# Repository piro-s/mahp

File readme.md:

# Music mini-amplifier with indicator:  
A simple two-channel amplifier on a chip TDA2822 with indicator.  

### Schemes:  
###### Amplifier_v0.1:  
[pdf](amplifier/docs/mahp_v0.1.pdf)  
###### Indicator_v0.1:  
[pdf](indicator/docs/indicator_v0.1.pdf)  

### Images:  
###### Amplifier_v0.1:  
top:  
  
bottom:  

###### Indicator_v0.1:  
top:  
  
bottom:  

###### gerber:  
Archive for production:  
[Amplifier_v0.1](https://github.com/piro-s/mahp/raw/master/amplifier/gerber/mahp_v0.1.zip)  
[Indicator_v0.1](https://github.com/piro-s/mahp/raw/master/indicator/gerber/indicator_v0.1.zip)

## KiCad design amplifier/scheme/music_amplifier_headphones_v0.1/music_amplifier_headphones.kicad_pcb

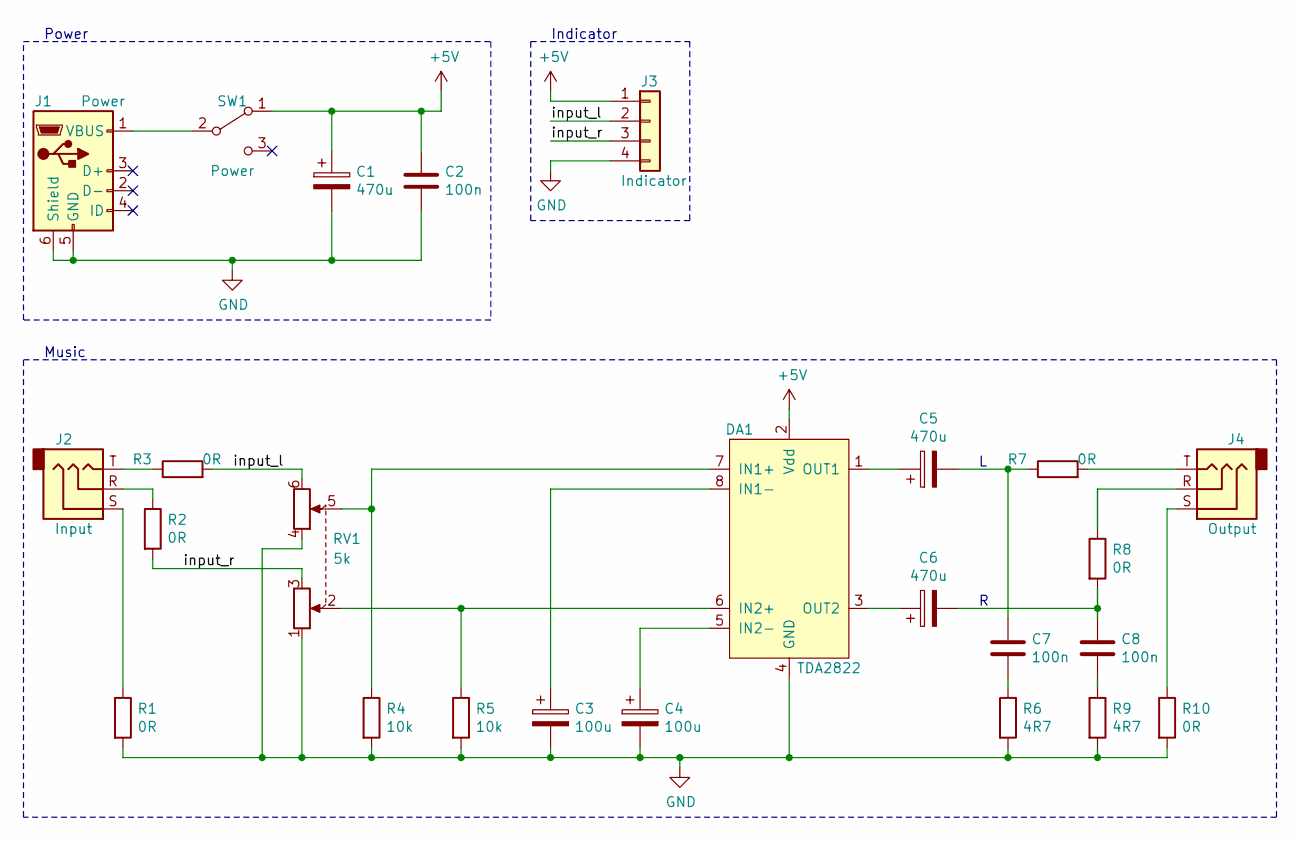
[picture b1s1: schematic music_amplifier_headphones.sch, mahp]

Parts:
C1, C5, C6: 470u; CP_Radial_D6.3mm_P2.50mm
C2, C7, C8: 100n; C_0603_1608Metric_Pad1.08x0.95mm_HandSolder
C3, C4: 100u; CP_Radial_D5.0mm_P2.00mm
DA1: TDA2822; SO-8_5.3x6.2mm_P1.27mm
J1: Power; USB_Micro-B_Amphenol_10104110_Horizontal
J2: Input; Jack_3.5mm_PJ322
J3: Indicator; Indicator_LM3915_female
J4: Output; Jack_3.5mm_PJ322
R1, R2, R3, R7, R8, R10: 0R; R_0603_1608Metric_Pad0.98x0.95mm_HandSolder
R4, R5: 10k; R_0603_1608Metric_Pad0.98x0.95mm_HandSolder
R6, R9: 4R7; R_0603_1608Metric_Pad0.98x0.95mm_HandSolder
RV1: 5k; Potentiometer_Alps_RK163_Dual_Horizontal
SW1: Power; MTS-102-C4

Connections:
+5V: C1.1, C2.1, DA1.2 (Vdd), J3.1, SW1.1 (A)
/input_l: J3.2, R3.2, RV1.6
/input_r: J3.3, R2.2, RV1.3
GND: C1.2, C2.2, C3.2, C4.2, DA1.4 (GND), J1.5 (GND), J1.6 (Shield), J3.4, R1.2, R4.2, R5.2, R6.2, R9.2, R10.2, RV1.1, RV1.4
unnamed: C3.1, DA1.8 (IN1-)
unnamed: C4.1, DA1.5 (IN2-)
unnamed: C5.1, DA1.1 (OUT1)
unnamed: C5.2, C7.1, R7.1
unnamed: C6.1, DA1.3 (OUT2)
unnamed: C6.2, C8.1, R8.2
unnamed: C7.2, R6.1
unnamed: C8.2, R9.1
unnamed: DA1.6 (IN2+), R5.1, RV1.2
unnamed: DA1.7 (IN1+), R4.1, RV1.5
unnamed: J1.1 (VBUS), SW1.2 (B)
unnamed: J2.R, R2.1
unnamed: J2.S, R1.1
unnamed: J2.T, R3.1
unnamed: J4.R, R8.1
unnamed: J4.S, R10.1
unnamed: J4.T, R7.2

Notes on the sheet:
Music
Power
Indicator

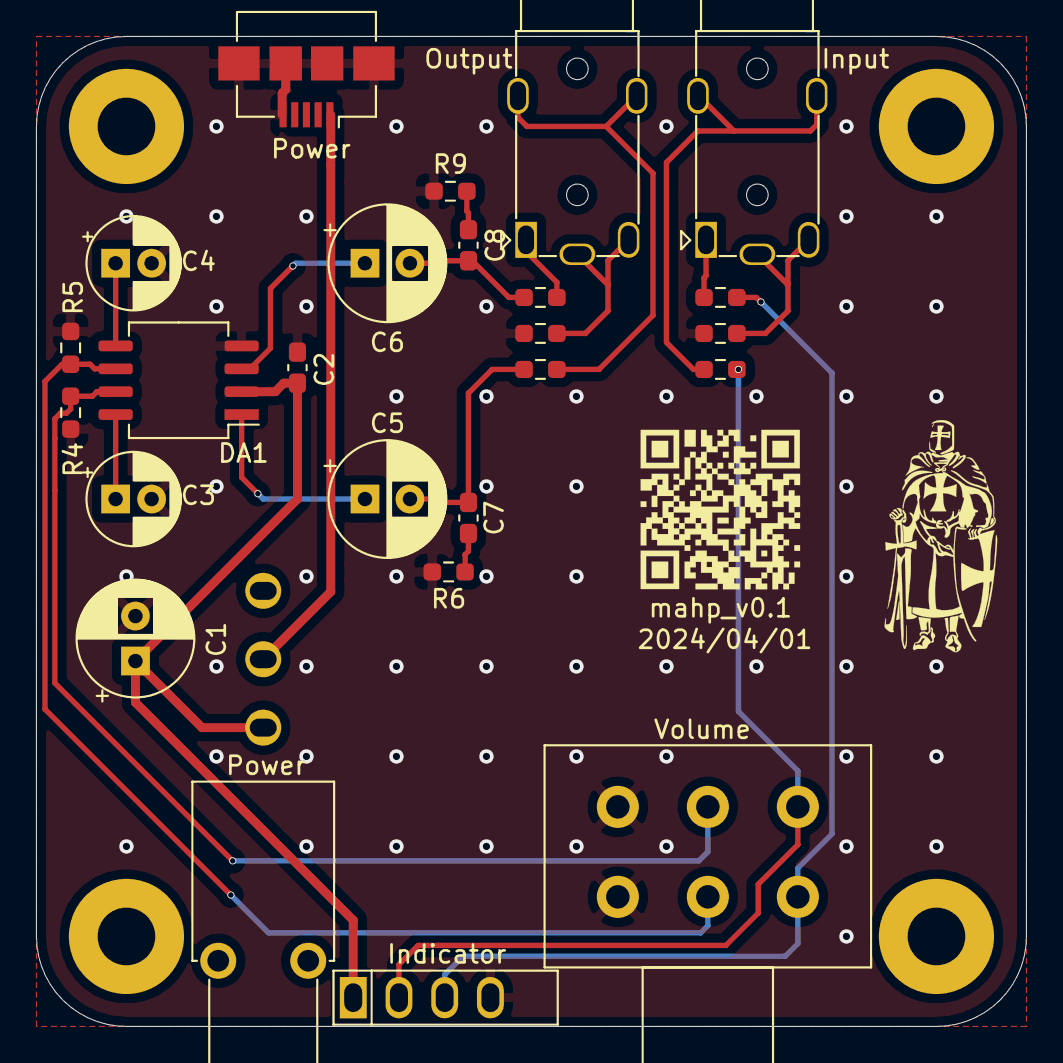
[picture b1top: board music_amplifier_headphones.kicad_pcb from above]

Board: 2 copper layers, 55.0 x 55.0 mm, 25 parts (0 on the bottom side), 21 nets.

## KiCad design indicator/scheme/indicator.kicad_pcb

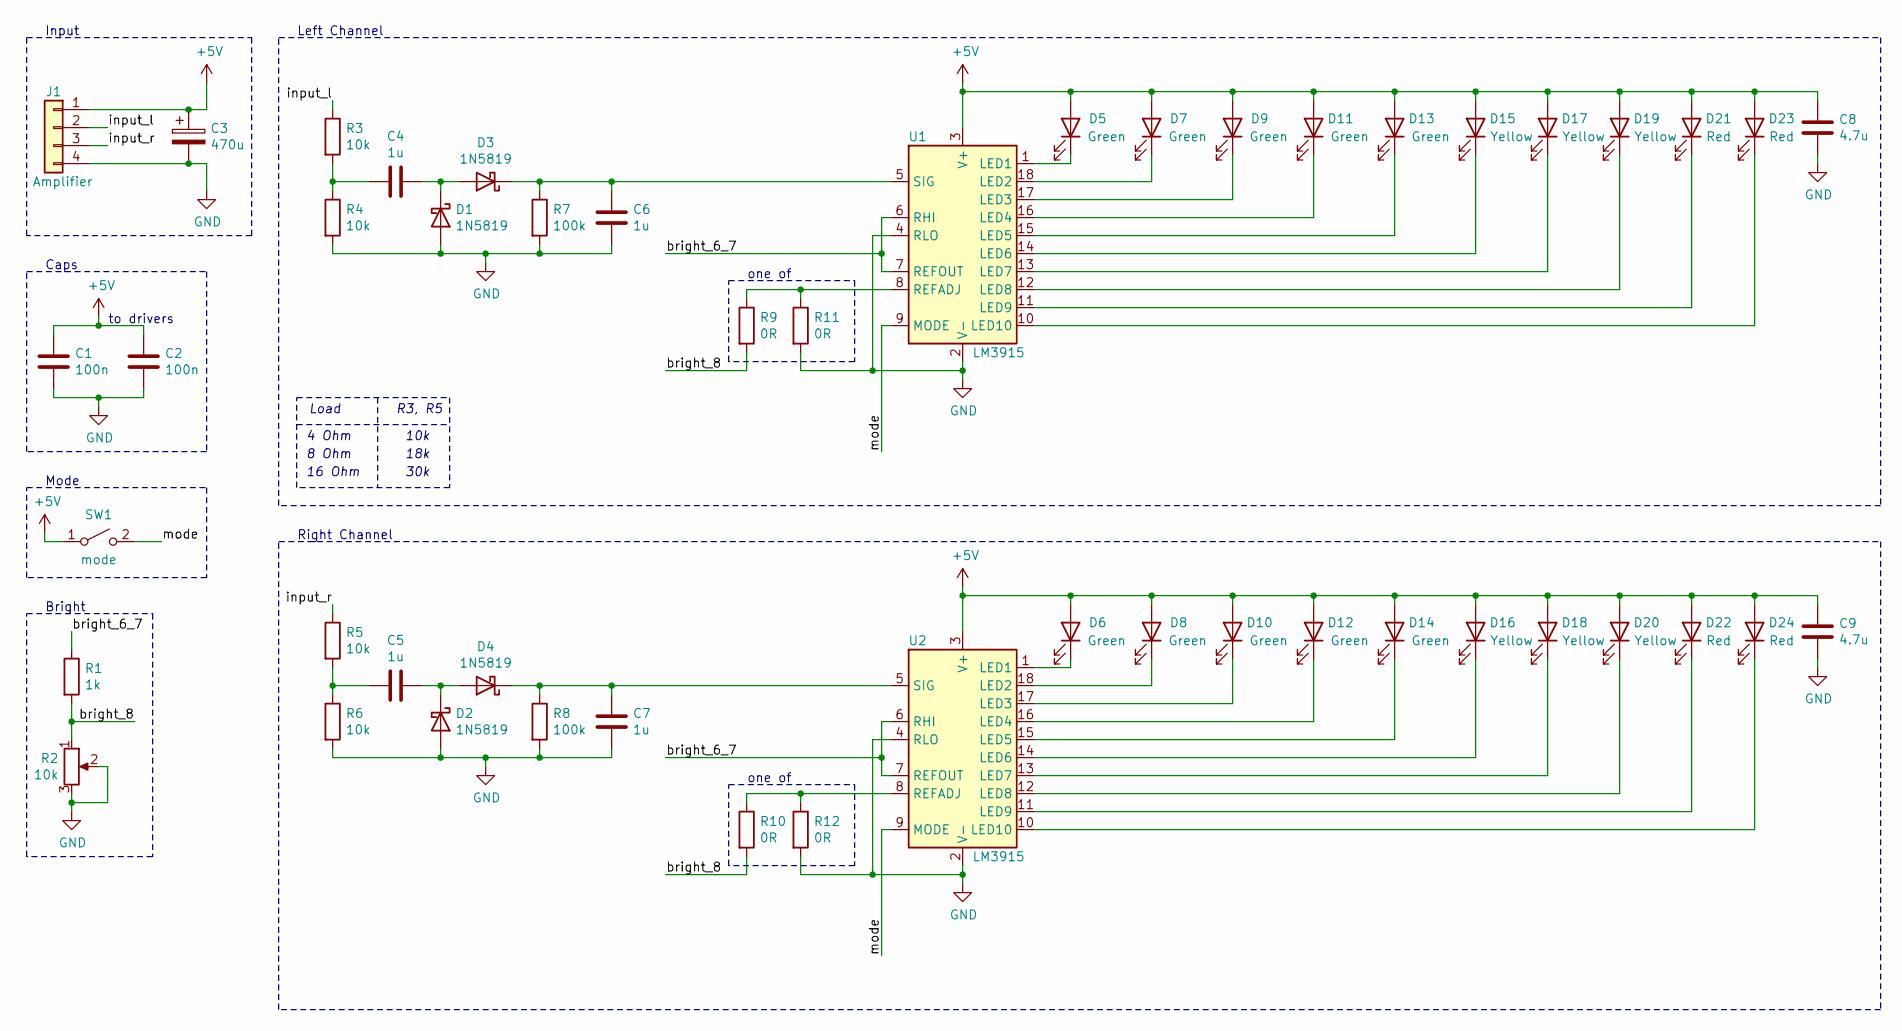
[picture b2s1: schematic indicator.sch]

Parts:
C1, C2: 100n; C_0603_1608Metric_Pad1.08x0.95mm_HandSolder
C3: 470u; CP_Radial_D6.3mm_P2.50mm
C4, C5, C6, C7: 1u; C_0603_1608Metric_Pad1.08x0.95mm_HandSolder
C8, C9: 4.7u; C_1206_3216Metric_Pad1.33x1.80mm_HandSolder
D1, D2, D3, D4: 1N5819; D_SOD-523
D5, D6, D7, D8, D9, D10, D11, D12, D13, D14: Green; LED_Rectangular_W3.9mm_H1.9mm
D15, D16, D17, D18, D19, D20: Yellow; LED_Rectangular_W3.9mm_H1.9mm
D21, D22, D23, D24: Red; LED_Rectangular_W3.9mm_H1.9mm
J1: Amplifier; Indicator_LM3915_male
R1: 1k; R_0603_1608Metric_Pad0.98x0.95mm_HandSolder
R2: 10k; Potentiometer_Bourns_3314J_Vertical
R3, R4, R5, R6: 10k; R_0603_1608Metric_Pad0.98x0.95mm_HandSolder
R7, R8: 100k; R_0603_1608Metric_Pad0.98x0.95mm_HandSolder
R9, R10, R11, R12: 0R; R_0603_1608Metric_Pad0.98x0.95mm_HandSolder
SW1: mode; PinHeader_1x02_P2.54mm_Vertical
U1, U2: LM3915; DIP-18_W7.62mm_LongPads

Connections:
+5V: C1.1, C2.1, C3.1, C8.1, C9.1, D5.2 (A), D6.2 (A), D7.2 (A), D8.2 (A), D9.2 (A), D10.2 (A), D11.2 (A), D12.2 (A), D13.2 (A), D14.2 (A), D15.2 (A), D16.2 (A), D17.2 (A), D18.2 (A), D19.2 (A), D20.2 (A), D21.2 (A), D22.2 (A), D23.2 (A), D24.2 (A), J1.1, SW1.1 (A), U1.3 (V+), U2.3 (V+)
/bright_6_7: R1.1, U1.6 (RHI), U1.7 (REFOUT), U2.6 (RHI), U2.7 (REFOUT)
/bright_8: R1.2, R2.1, R9.2, R10.2
/input_l: J1.2, R3.1
/input_r: J1.3, R5.1
/mode: SW1.2 (B), U1.9 (MODE), U2.9 (MODE)
GND: C1.2, C2.2, C3.2, C6.1, C7.1, C8.2, C9.2, D1.2 (A), D2.2 (A), J1.4, R2.2, R2.3, R4.2, R6.2, R7.2, R8.2, R11.2, R12.2, U1.2 (V-), U1.4 (RLO), U2.2 (V-), U2.4 (RLO)
unnamed: C4.1, D1.1 (K), D3.2 (A)
unnamed: C4.2, R3.2, R4.1
unnamed: C5.1, D2.1 (K), D4.2 (A)
unnamed: C5.2, R5.2, R6.1
unnamed: C6.2, D3.1 (K), R7.1, U1.5 (SIG)
unnamed: C7.2, D4.1 (K), R8.1, U2.5 (SIG)
unnamed: D5.1 (K), U1.1 (LED1)
unnamed: D6.1 (K), U2.1 (LED1)
unnamed: D7.1 (K), U1.18 (LED2)
unnamed: D8.1 (K), U2.18 (LED2)
unnamed: D9.1 (K), U1.17 (LED3)
unnamed: D10.1 (K), U2.17 (LED3)
unnamed: D11.1 (K), U1.16 (LED4)
unnamed: D12.1 (K), U2.16 (LED4)
unnamed: D13.1 (K), U1.15 (LED5)
unnamed: D14.1 (K), U2.15 (LED5)
unnamed: D15.1 (K), U1.14 (LED6)
unnamed: D16.1 (K), U2.14 (LED6)
unnamed: D17.1 (K), U1.13 (LED7)
unnamed: D18.1 (K), U2.13 (LED7)
unnamed: D19.1 (K), U1.12 (LED8)
unnamed: D20.1 (K), U2.12 (LED8)
unnamed: D21.1 (K), U1.11 (LED9)
unnamed: D22.1 (K), U2.11 (LED9)
unnamed: D23.1 (K), U1.10 (LED10)
unnamed: D24.1 (K), U2.10 (LED10)
unnamed: R10.1, R12.1, U2.8 (REFADJ)
unnamed: R9.1, R11.1, U1.8 (REFADJ)

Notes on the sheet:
Input
Caps
to drivers
one of
Left Channel
Right Channel
Mode
Bright
Load
R3, R5
4 Ohm
8 Ohm
16 Ohm
10k
18k
30k

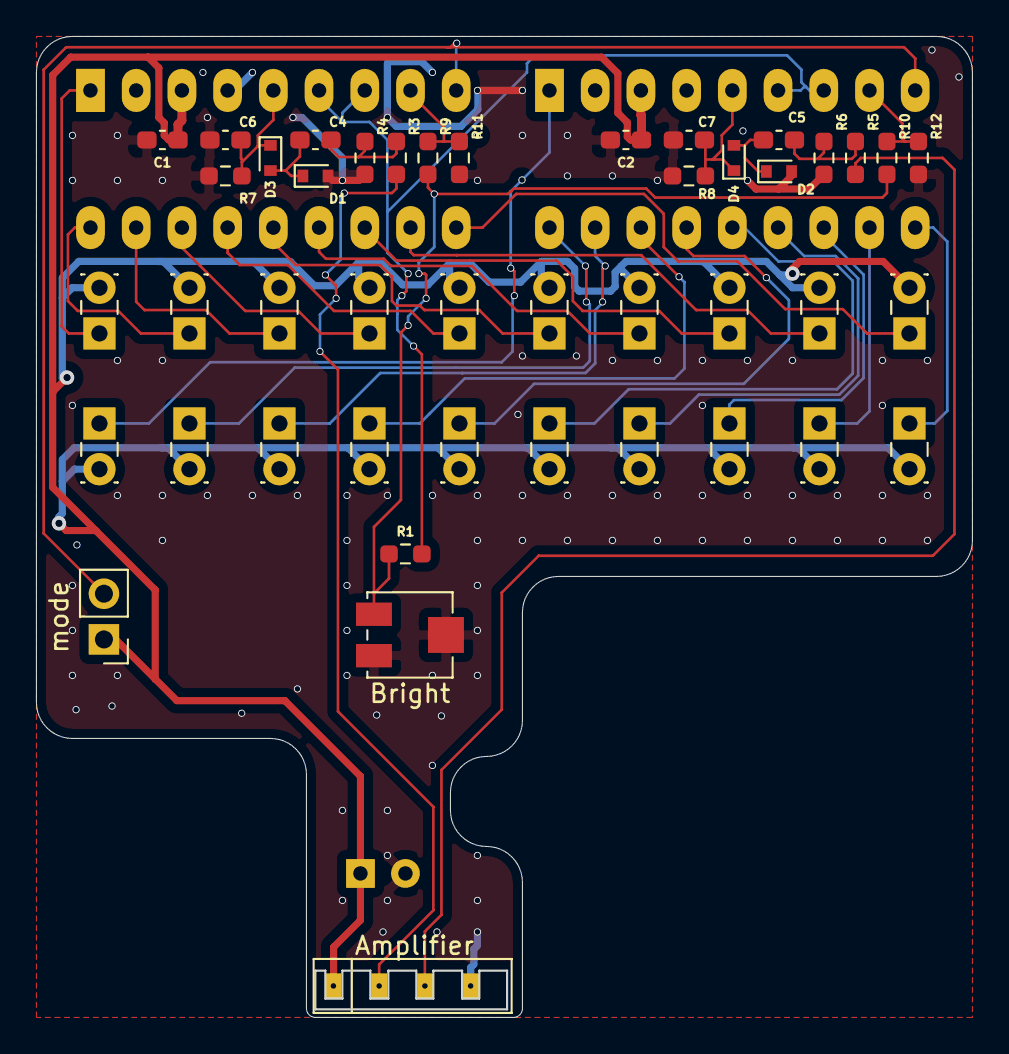
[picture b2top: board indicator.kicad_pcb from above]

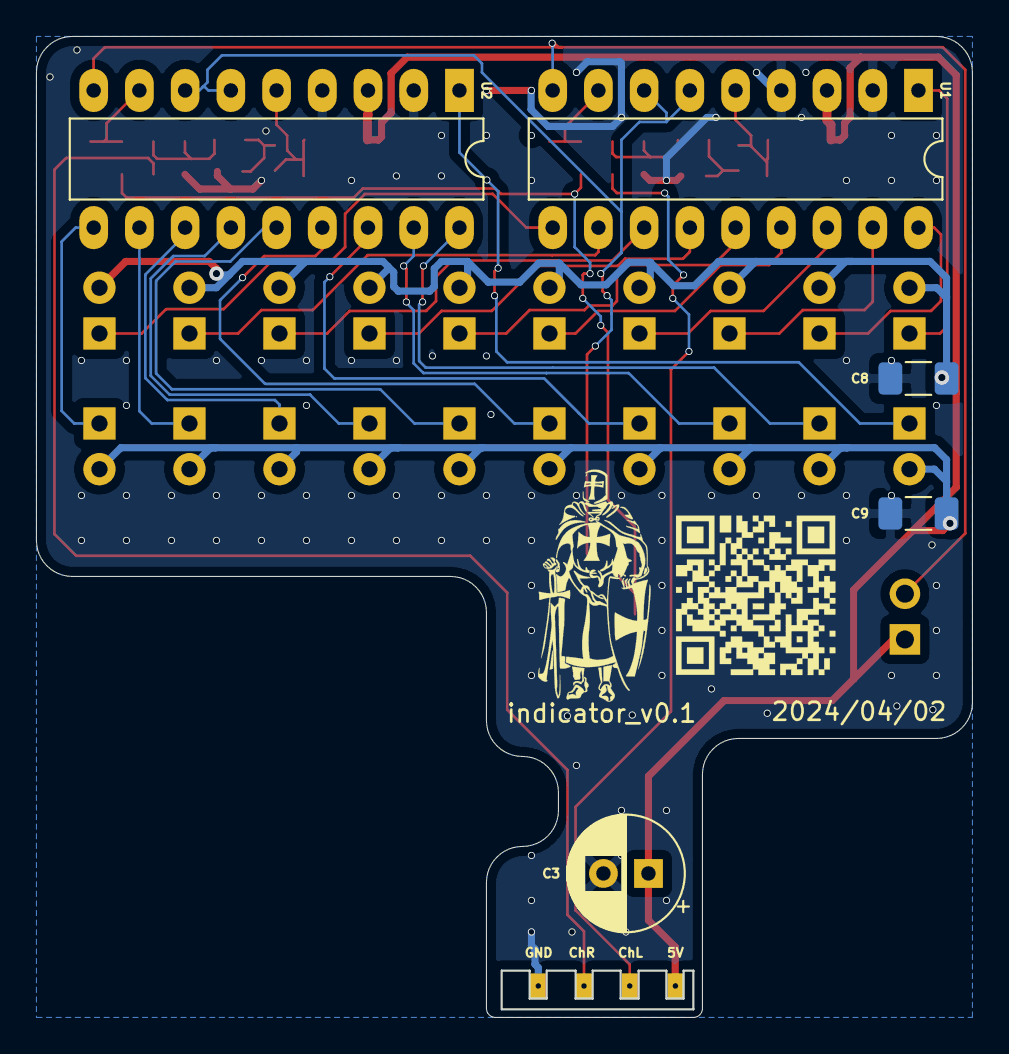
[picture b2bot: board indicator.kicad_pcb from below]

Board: 2 copper layers, 51.9 x 54.4 mm, 49 parts (5 on the bottom side), 35 nets.

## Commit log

2024-04-02 Initial
2024-04-02 small: Gerber links
    Fix gerber links in readme.
2024-05-02 small: QR code
    Change QR code from github to site.
